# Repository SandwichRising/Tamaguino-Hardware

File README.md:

# Tamaguino-Hardware
### PCB and Case Design Repository

This github is an open-source hardware repository and buildlog to make a case and PCB assembly for my friend Alojz Jakob's Tamaguino virtual pet [firmware](https://alojzjakob.github.io/Tamaguino/). Feel free to use and edit the design, and to contact me if you would like fabricated parts. 

<br>

## Design

This project was planned as a 3-day sprint. One day was spent brainstorming and sketching a workable layout from available parts. The next day was spent drafting a schematic and practical, cuttable 3d models for the case and PCB using both KiCad and Fusion360. The third day was spent writing CAM toolpathing, fabricating the actual case and PCB from stock material, assembling and soldering parts together, and programming the Tamaguino firmware onto the ATmega328P microprocessor to finish the project. 

<br>

<br>
<br>

## Fabrication

An Australian Lacewood board was selected from a local hardwood store to make cases. One description used for the surface of this wood is "reptillian", so I thought it would be perfect to house a dinosaur pet. Fusion360 was used to create the CAM instructions for the CNC machine using the designed models. A Onefinity CNC machine was used to process the wood board and some PCB blank material into actual cases and PCBs. 

<br>
<br>

## Repository and BOM

The [KiCad folder](./kicad7.0) includes the schematic and PCB layout, as well as a plotOutput subfolder with .dxf and .svg exports. KiCad's plotOutput files were used directly in Fusion360 to program the CAM instructions to cut the PCBs. An earlier version of KiCad was used during the project, and the design files have now been resaved with KiCad v7.0. The Eco1 User layer was used to draw the plexiglass shield, and the tamaguino-Eco1_User.svg file in the plotOutput subfolder was used by a laser cutter to cut the actual shield. The case was drawn in Fusion360 using plotOutput files as reference. It has been included in the repository as an .stl file which may be machined or 3d printed. A drill must be used to widen screw holes to match M2 or whichever screw is selected to hold the PCB in place, the model only has a small divot indicating where the holes belong.

<br>
<br>

### Components used in build:

These are the actual parts used in the pictured assemblies. As some of the parts came in kits or multipacks, cheaper alternatives could be found using these parts as reference.

* Micro USB Adapter: https://www.amazon.com/gp/product/B07W844N43
* I2C Oled Screen: https://www.amazon.com/gp/product/B07VDXYDVY
* ATmega328P: https://www.digikey.com/en/products/detail/microchip-technology/ATMEGA328P-Pdigikey%2028dip%20socketU/1914589
* 28-Dip Socket: https://www.digikey.com/en/products/detail/adam-tech/ICS-328-T/9832859
* 16MHz Ceramic Resonator: https://www.adafruit.com/product/1873
* 6mm Buttons: https://www.adafruit.com/product/1490
* 6mm M2 Standoffs and Screws from Multikit: https://www.amazon.com/gp/product/B075K3QBMX
* Speaker: https://www.amazon.com/gp/product/B01GJLE5BS/
* Generic LED from Kit: https://www.amazon.com/gp/product/B07DQQCXV9
* As well as both a 1k and 10k ohm resistor.

<br>
<br>

### A Note on Programming

As this design uses a bare processor chip, another AVR is used to program the ATmega328P. In my case, I used an Arduino flashed with ArduinoISP as a programmer and another Arduino board with the processor removed as a socket to host the bare 328P. A breadboard could instead be used for the socket to program, as there just needs to be an ICSP connection between the programmer and socket. 

<br>
<br>

Thanks for taking a look!

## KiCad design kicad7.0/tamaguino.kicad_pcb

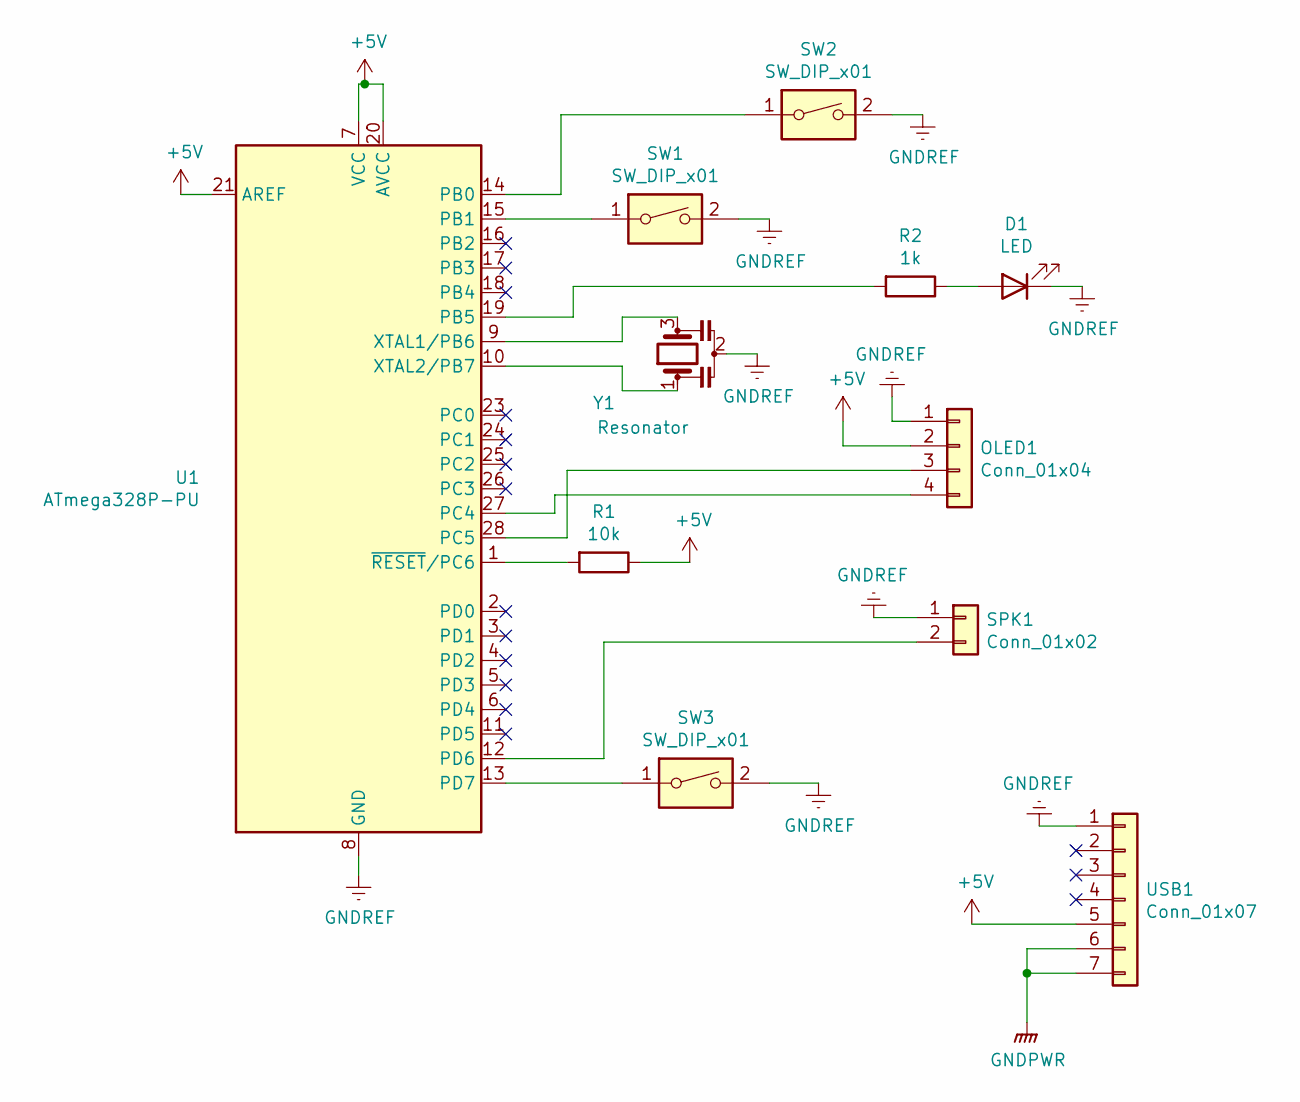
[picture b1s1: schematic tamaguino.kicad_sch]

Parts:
D1: LED; LED_D5.0mm
OLED1: Conn_01x04; PinHeader_1x04_P2.54mm_Vertical
R1: 10k; R_Axial_DIN0207_L6.3mm_D2.5mm_P7.62mm_Horizontal
R2: 1k; R_Axial_DIN0207_L6.3mm_D2.5mm_P7.62mm_Horizontal
SPK1: Conn_01x02; C_Radial_D12.5mm_H20.0mm_P5.00mm
SW1, SW2, SW3: SW_DIP_x01; SW_PUSH_6mm
U1: ATmega328P-PU; DIP-28_W7.62mm
USB1: Conn_01x07; USB-AMAZON(PERSONAL_LIBRARY)
Y1: Resonator; Resonator-3Pin_W7.0mm_H2.5mm

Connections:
+5V: OLED1.2, R1.1, U1.7 (VCC), U1.20 (AVCC), U1.21 (AREF), USB1.5
GNDPWR: USB1.6, USB1.7
GNDREF: D1.1 (K), OLED1.1, SPK1.1, SW1.2, SW2.2, SW3.2, U1.8 (GND), U1.22 (GND), USB1.1, Y1.2
unnamed: D1.2 (A), R2.1
unnamed: OLED1.3, U1.28 (PC5)
unnamed: OLED1.4, U1.27 (PC4)
unnamed: R1.2, U1.1 (~RESET/PC6)
unnamed: R2.2, U1.19 (PB5)
unnamed: SPK1.2, U1.12 (PD6)
unnamed: SW1.1, U1.15 (PB1)
unnamed: SW2.1, U1.14 (PB0)
unnamed: SW3.1, U1.13 (PD7)
unnamed: U1.9 (XTAL1/PB6), Y1.3
unnamed: U1.10 (XTAL2/PB7), Y1.1

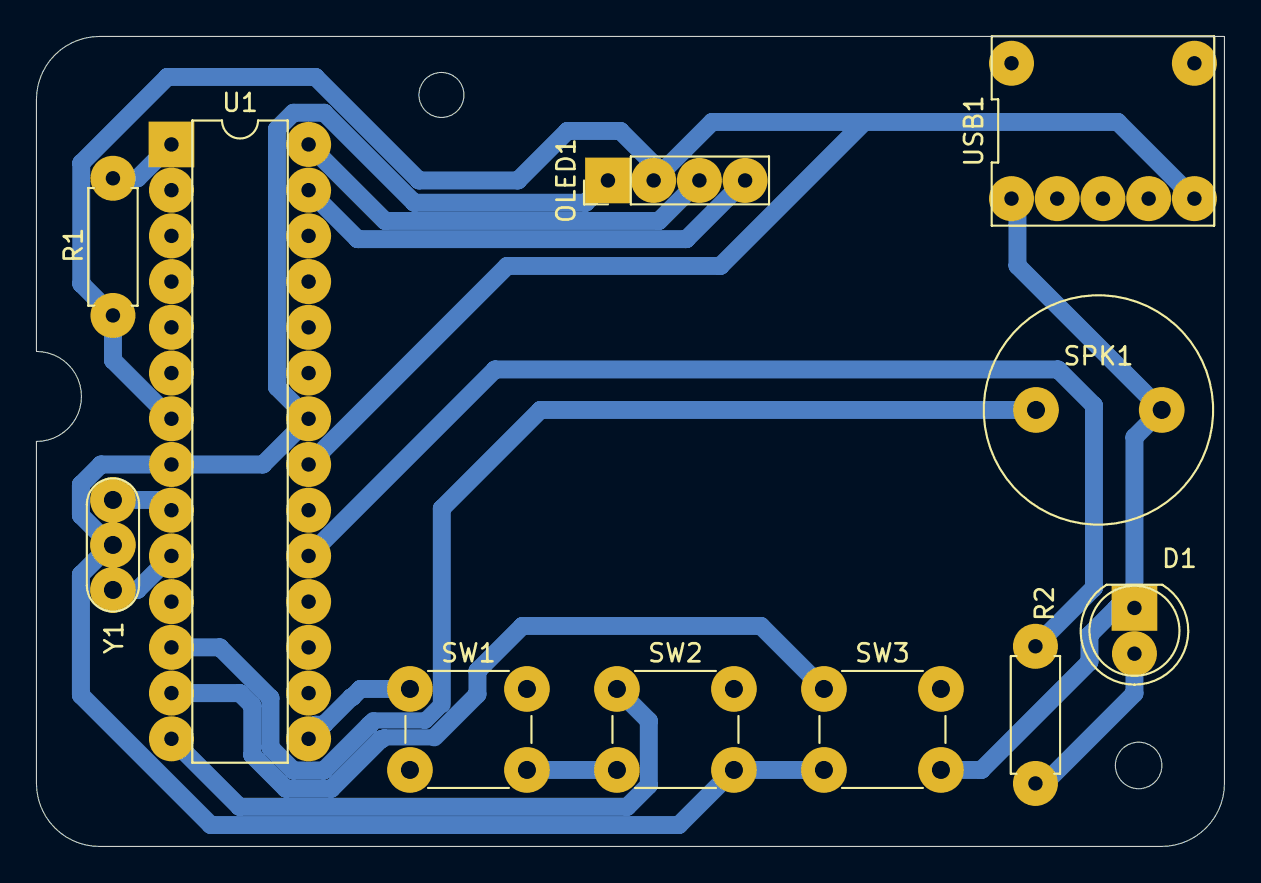
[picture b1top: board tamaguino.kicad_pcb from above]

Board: 2 copper layers, 66.0 x 45.0 mm, 11 parts (0 on the bottom side), 14 nets.

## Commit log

2024-04-07 adding media files
2024-04-07 media renames, kicad added
2024-04-07 update sketch
2024-04-08 adding media and stl
